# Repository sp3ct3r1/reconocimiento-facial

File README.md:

# reconocimiento-facial

### en este proyecto se muestra como diseñar y crear un control de acceso mediante una camara, y usando un reconocimiento facial para saber cuando un alumno esta presente, y/o concederle el acceso al establecimiento. tambien se puede usar en otros ambitos laborales, como oficinas, empresas, etc. todo para saber la asistencia y productividad de los trabajadores o del publico.

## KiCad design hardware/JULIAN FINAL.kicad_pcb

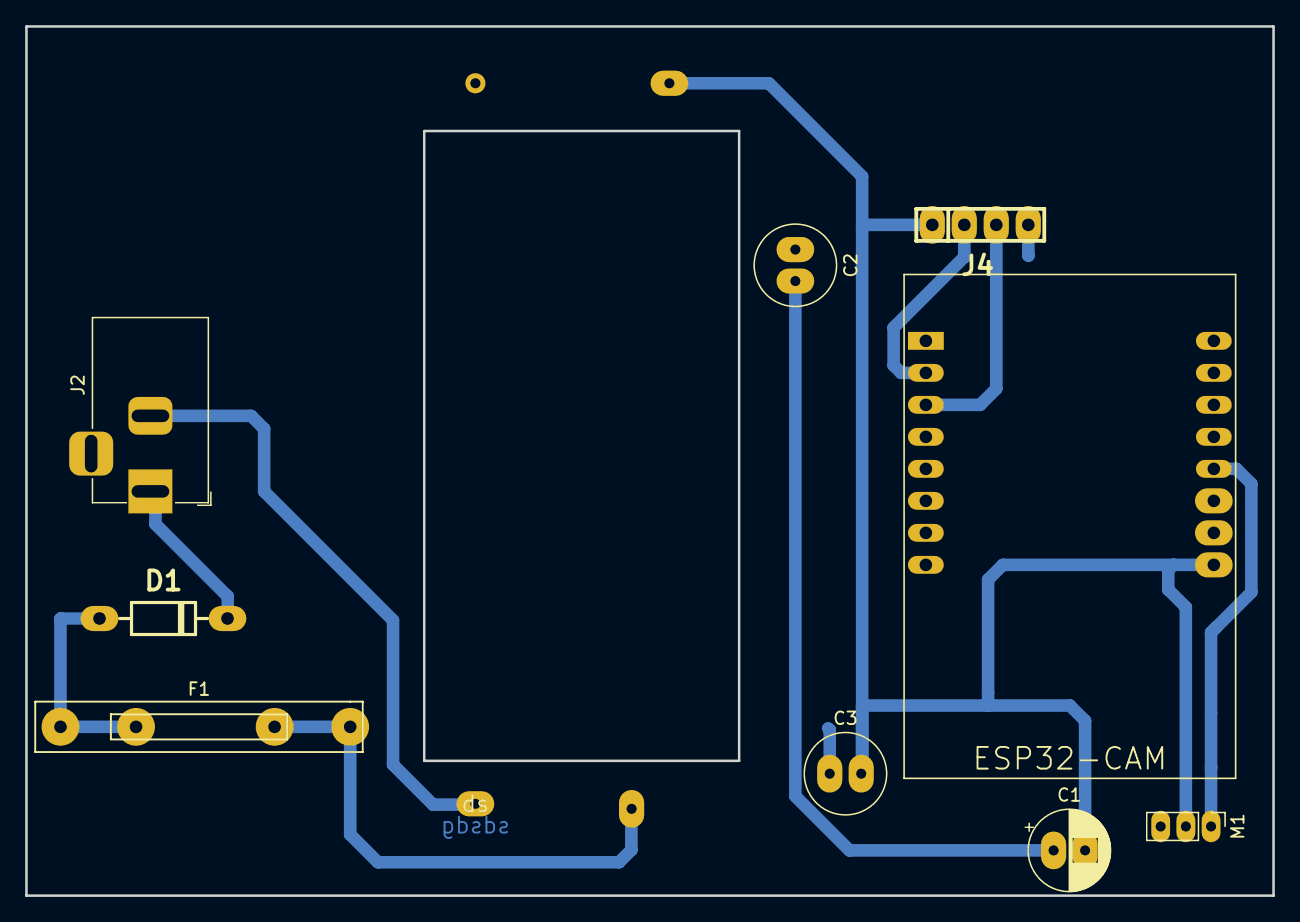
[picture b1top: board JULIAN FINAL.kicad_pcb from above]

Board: 2 copper layers, 99.0 x 69.0 mm, 10 parts (0 on the bottom side), 8 nets.

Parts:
C1: C_Polarized; CP_Radial_D6.3mm_P2.50mm
C2, C3: 0,1uf; C_Radial_D6.3mm_H7.0mm_P2.50mm
D1: 1N4148WT; DO-41
F1: Fuse; FUSIBLE
G´pio12: ESP32-CAM; ESP32S-CAM
J2: Jack-DC; BarrelJack_Horizontal
J4: HEADER_4; pin_strip_4
M1: Motor_Servo_Futaba_J; PinHeader_1x03_P2.00mm_Vertical
ds: sdsdg

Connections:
5V: C1.2, C3.2, G´pio12.9, J4.1
12V: D1.2 (A), J2.1
GND: C2.1, C3.1, G´pio12.10, J4.4, M1.3 (-)
unnamed: C1.1, C2.2
unnamed: G´pio12.2, G´pio12.3, J4.2
unnamed: G´pio12.12, M1.1 (PWM)
unnamed: D1.1 (K), F1.1
PGND: J2.2, ds.1

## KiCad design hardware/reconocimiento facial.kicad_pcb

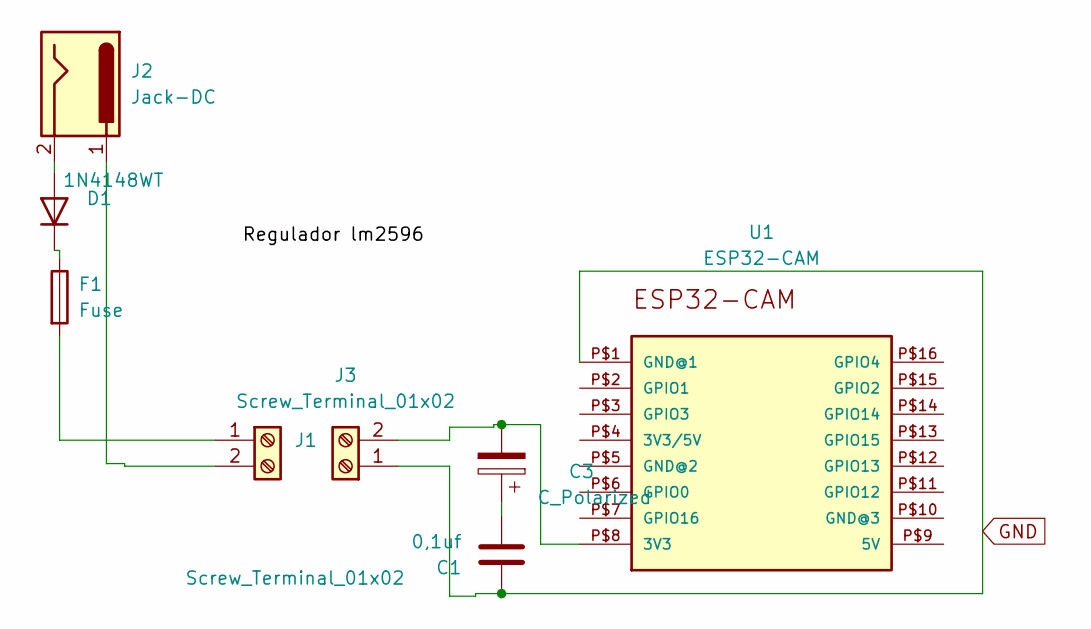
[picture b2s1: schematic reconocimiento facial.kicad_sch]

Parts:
C1: 0,1uf; C_Radial_D6.3mm_H7.0mm_P2.50mm
C3: C_Polarized; CP_Radial_D6.3mm_P2.50mm
D1: 1N4148WT; DO-41
F1: Fuse; FUSIBLE
J1, J3: Screw_Terminal_01x02; BORNERA2_AZUL
J2: Jack-DC; BarrelJack_SwitchcraftConxall_RAPC10U_Horizontal
U1: ESP32-CAM; ESP32S-CAM

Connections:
GND: C1.1, J3.1, U1.P$1 (GND@1)
unnamed: C1.2, C3.1
unnamed: D1.2 (A), J2.2
unnamed: D1.1 (K), F1.1
unnamed: F1.2, J1.1
unnamed: J1.2, J2.1
unnamed: C3.2, J3.2, U1.P$8 (3V3)

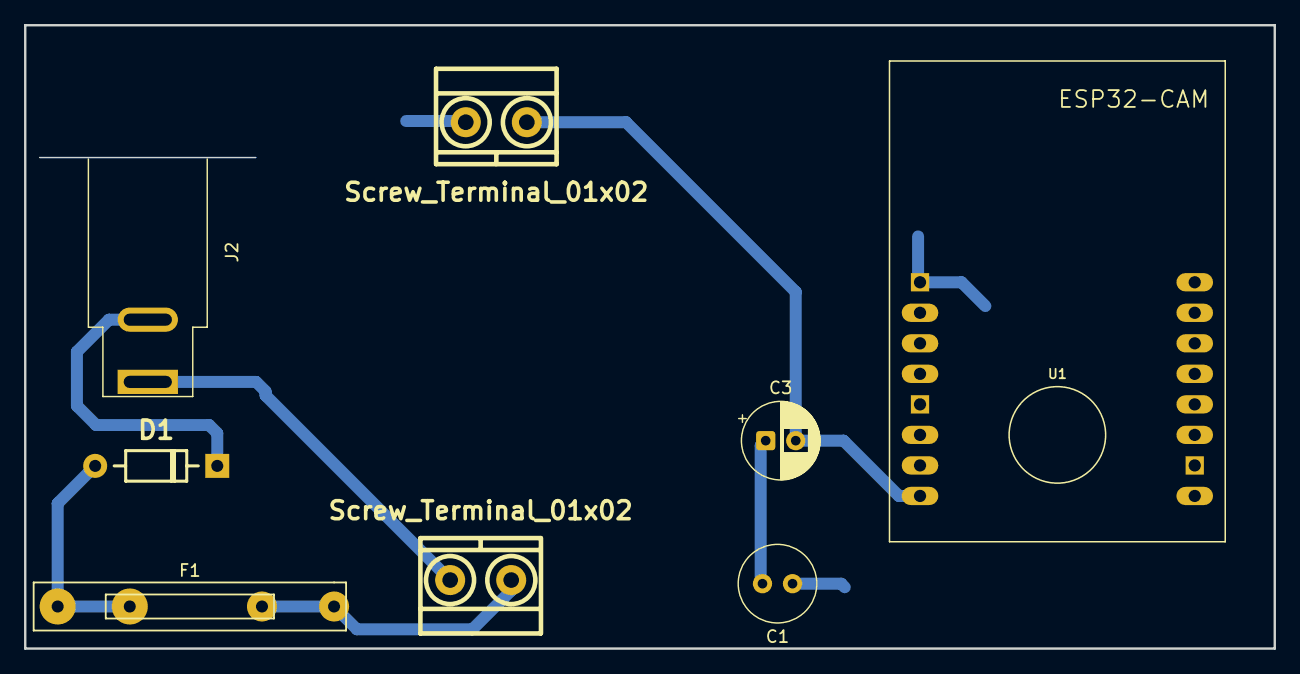
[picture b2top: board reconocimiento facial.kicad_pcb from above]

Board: 2 copper layers, 104.0 x 51.9 mm, 8 parts (0 on the bottom side), 7 nets.
